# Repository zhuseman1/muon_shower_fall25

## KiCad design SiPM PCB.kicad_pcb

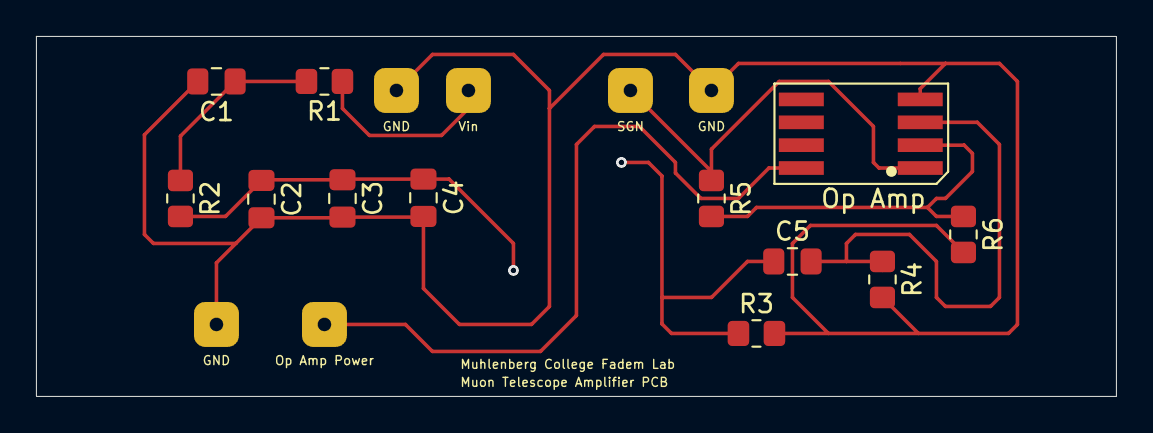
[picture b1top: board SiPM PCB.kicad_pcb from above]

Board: 2 copper layers, 60.0 x 20.0 mm, 19 parts (1 on the bottom side), 9 nets.

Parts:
C1, C3, C4: 10nF; C_0805_2012Metric_Pad1.18x1.45mm_HandSolder
C2: 10nf; C_0805_2012Metric_Pad1.18x1.45mm_HandSolder
C5: 100 nF; C_0805_2012Metric_Pad1.18x1.45mm_HandSolder
GND: SolderWirePad_1x01_SMD_1x2mm
GND#2, GND#3: SolderWirePad_1x01_SMD_1x2mm
Op Amp: SOIC-8
Op Amp Power: SolderWirePad_1x01_SMD_1x2mm
R1, R2, R3: 49.9; R_0805_2012Metric_Pad1.20x1.40mm_HandSolder
R4, R6: 1K; R_0805_2012Metric_Pad1.20x1.40mm_HandSolder
R5: 39K; R_0805_2012Metric_Pad1.20x1.40mm_HandSolder
SGN: SolderWirePad_1x01_SMD_1x2mm
SiPM_1: SiPM_Footprint
Vin: SolderWirePad_1x01_SMD_1x2mm

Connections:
+29.4V: R1.1, Vin.1
GND: C1.2, C2.2, C3.2, C4.2, GND.1, GND#2.1, GND#3.1, Op Amp.4, R3.2, R4.2, R6.2
unnamed: C1.1, R1.2, R2.1
unnamed: Op Amp.8, Op Amp Power.1
unnamed: Op Amp.1, R5.1, SGN.1
unnamed: C5.1, R3.1, SiPM_1.1 (Anode)
unnamed: C2.1, C3.1, C4.1, R2.2, SiPM_1.3 (Cathode)
unnamed: C5.2, Op Amp.3, R4.1
unnamed: Op Amp.2, R5.2, R6.1

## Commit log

2025-11-20 Create j
2025-11-20 Rename MASTER-UNO_shower-code_HH-MM-timestamp_7-1.ino to Arduino-Python_Data_Acquisition_code/MASTER-UNO_shower-code_HH-MM-timestamp_7-1.ino
2026-02-26 Create MASTER-UNO_synced_code_2-26-2026
